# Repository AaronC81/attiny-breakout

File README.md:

# ATtiny Breakout

This is a little breakout board for easy programming of DIP ATtiny25/45/85 chips on a breadboard.

(I got mine fabricated by [JLC](https://jlcpcb.com/), which worked out at about £5.50 for five boards, including delivery.)

It has a 6-pin ISP header for programming, so you'll need an AVR programmer. It also passes the ATtiny's pins through headers on the bottom of the board; this means you can plug it straight into a breadboard, and once you're done programming your ATtiny, simply remove the breakout and replace it with the lone chip.

It's been tested with an ATtiny85 (but should work on 25 and 45 too) and a Pololu USB AVR Programmer.

## Creating Gerbers

This repo contains all the KiCad files you should need. Open up the project in KiCad and build gerbers as required for your fabricator of choice!

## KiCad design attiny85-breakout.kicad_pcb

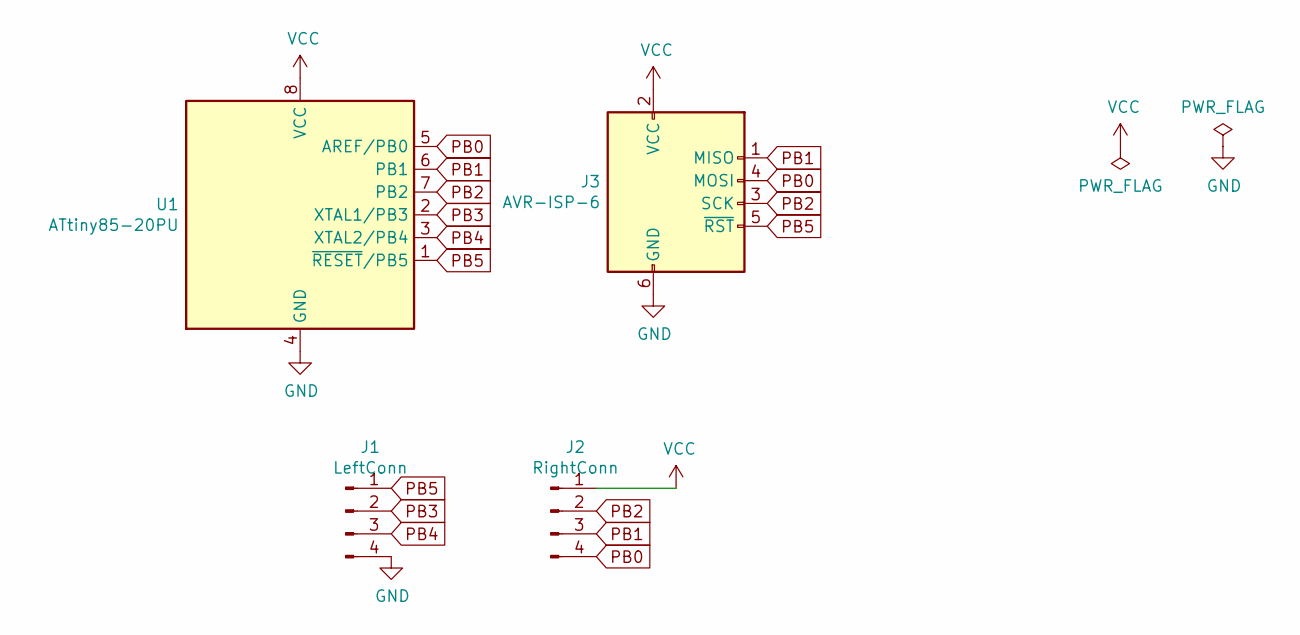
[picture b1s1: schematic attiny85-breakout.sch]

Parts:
J1: LeftConn; PinHeader_1x04_P2.54mm_Vertical_FlippedModel
J2: RightConn; PinHeader_1x04_P2.54mm_Vertical_FlippedModel
J3: AVR-ISP-6; PinHeader_2x03_P2.54mm_Vertical
U1: ATtiny85-20PU; DIP-8_W7.62mm

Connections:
GND: J1.4, J3.6 (GND), U1.4 (GND)
PB0: J2.4, J3.4 (MOSI), U1.5 (AREF/PB0)
PB1: J2.3, J3.1 (MISO), U1.6 (PB1)
PB2: J2.2, J3.3 (SCK), U1.7 (PB2)
PB3: J1.2, U1.2 (XTAL1/PB3)
PB4: J1.3, U1.3 (XTAL2/PB4)
PB5: J1.1, J3.5 (~RST), U1.1 (~RESET~/PB5)
VCC: J2.1, J3.2 (VCC), U1.8 (VCC)

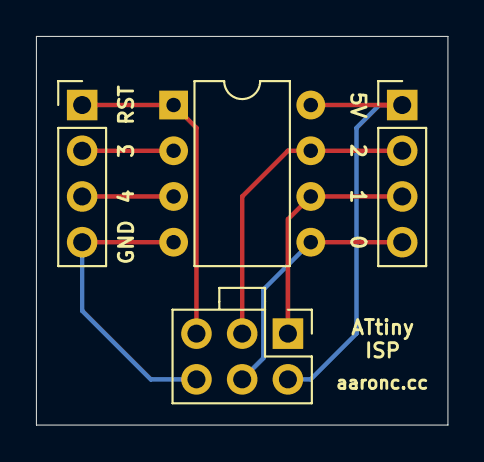
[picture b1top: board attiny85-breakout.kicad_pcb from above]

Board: 2 copper layers, 22.9 x 21.6 mm, 4 parts (0 on the bottom side), 8 nets.

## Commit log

2020-07-10 Compress images a bit
